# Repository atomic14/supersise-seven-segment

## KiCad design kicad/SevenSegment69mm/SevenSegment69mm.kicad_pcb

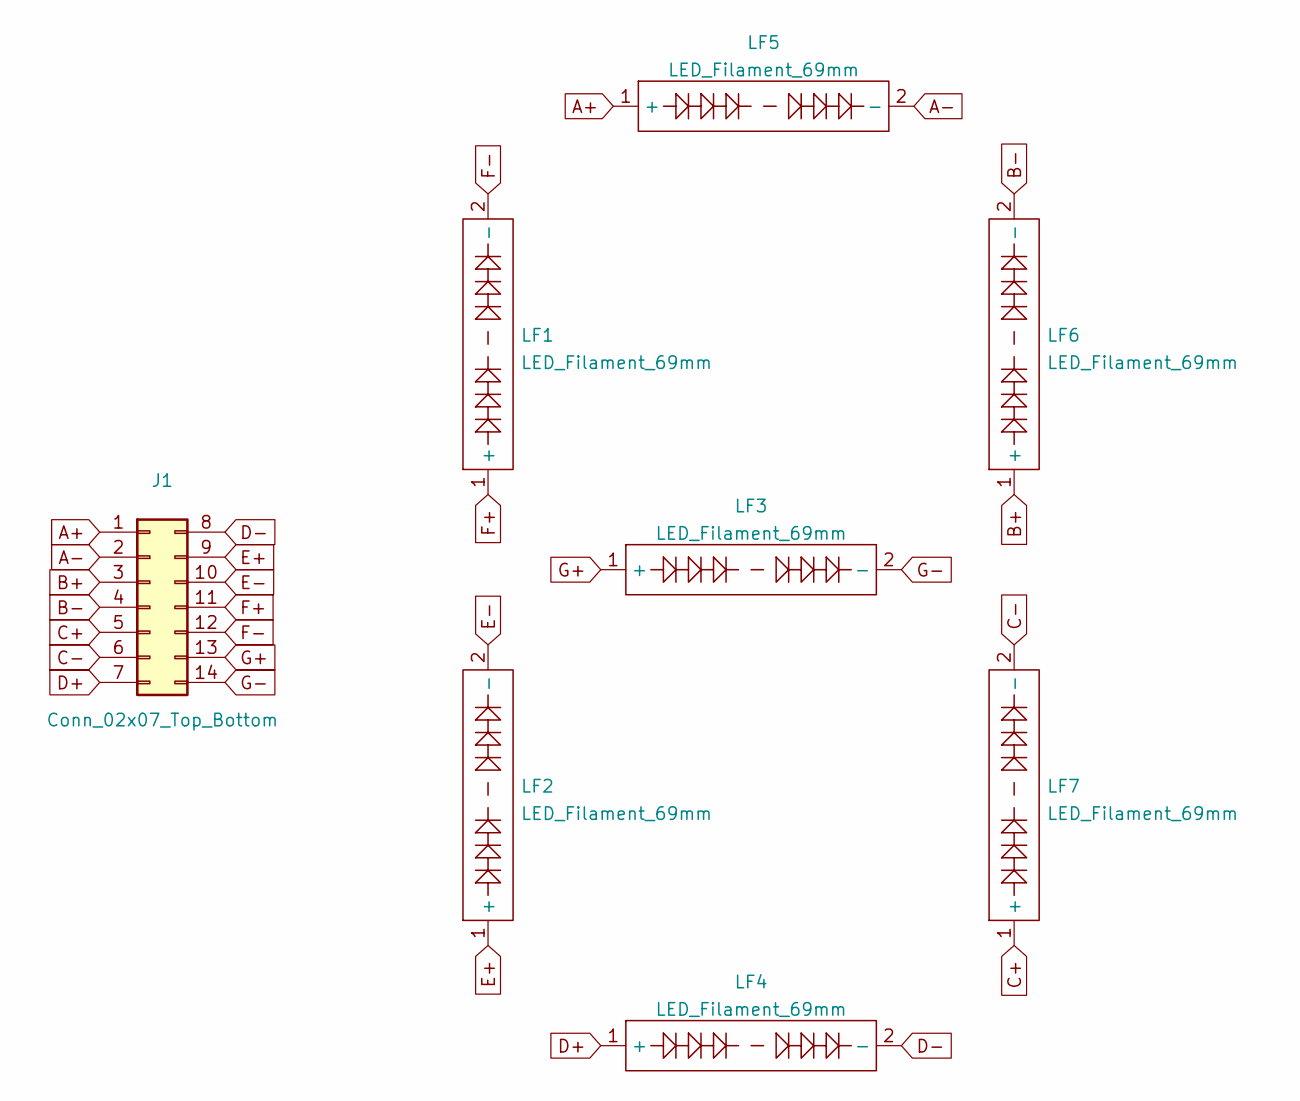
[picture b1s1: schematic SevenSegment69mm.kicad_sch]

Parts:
J1: Conn_02x07_Top_Bottom; PinHeader_2x07_P2.54mm_Horizontal
LF1, LF2, LF3, LF4, LF5, LF6, LF7: LED_Filament_69mm

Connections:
A+: J1.1, LF5.1 (+)
A-: J1.2, LF5.2 (-)
B+: J1.3, LF6.1 (+)
B-: J1.4, LF6.2 (-)
C+: J1.5, LF7.1 (+)
C-: J1.6, LF7.2 (-)
D+: J1.7, LF4.1 (+)
D-: J1.8, LF4.2 (-)
E+: J1.9, LF2.1 (+)
E-: J1.10, LF2.2 (-)
F+: J1.11, LF1.1 (+)
F-: J1.12, LF1.2 (-)
G+: J1.13, LF3.1 (+)
G-: J1.14, LF3.2 (-)

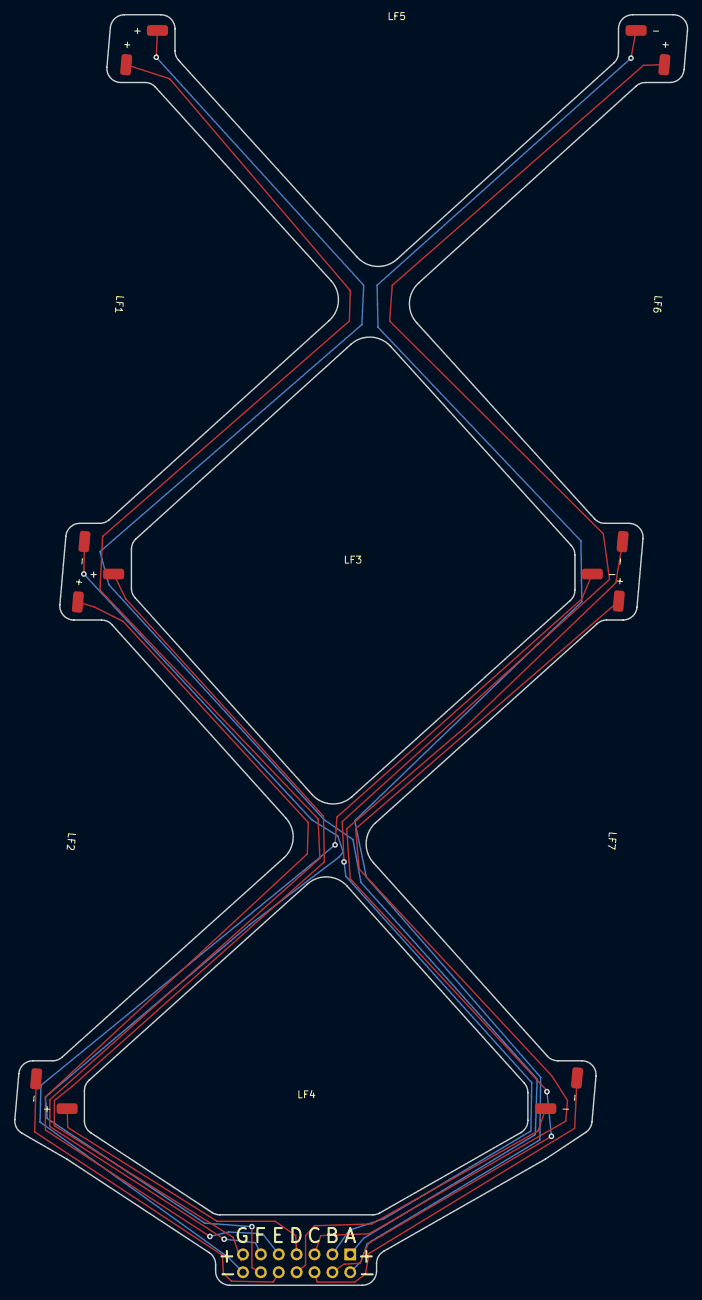
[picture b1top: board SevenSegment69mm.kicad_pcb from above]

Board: 2 copper layers, 95.6 x 180.5 mm, 8 parts (0 on the bottom side), 14 nets.

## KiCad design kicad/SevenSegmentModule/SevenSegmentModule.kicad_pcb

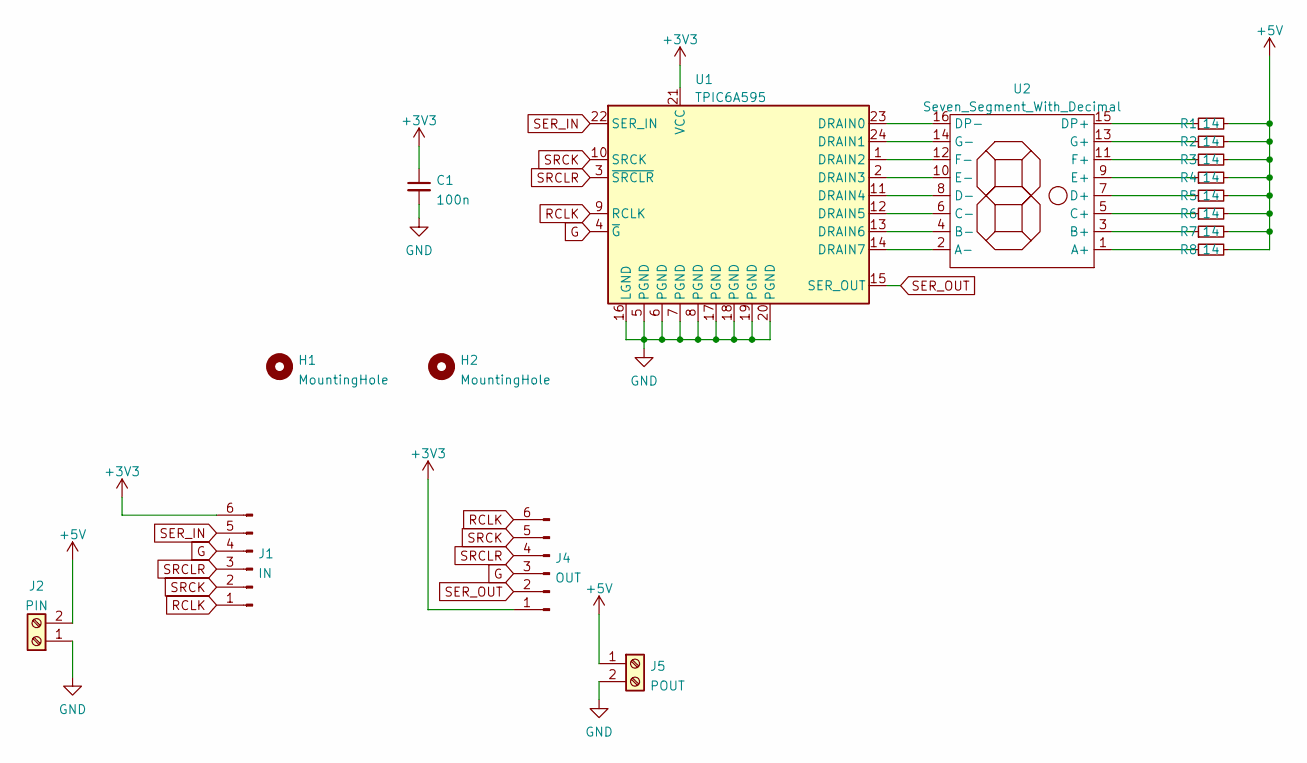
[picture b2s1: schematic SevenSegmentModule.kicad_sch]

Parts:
C1: 100n; C_0603_1608Metric
H1, H2: MountingHole; MountingHole_3.2mm_M3
J1: IN; PinHeader_1x06_P2.54mm_Horizontal
J2: PIN; TerminalBlock_Phoenix_MKDS-1,5-2-5.08_1x02_P5.08mm_Horizont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
J4: OUT; PinHeader_1x06_P2.54mm_Horizontal
J5: POUT; TerminalBlock_Phoenix_MKDS-1,5-2-5.08_1x02_P5.08mm_Horizont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
R1, R2, R3, R4, R5, R6, R7, R8: 14; R_0805_2012Metric
U1: TPIC6A595; SOIC-24W_7.5x15.4mm_P1.27mm
U2: Seven_Segment_With_Decimal; Segen_Segment_69mm_with_dp

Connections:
+3V3: C1.1, J1.6, J4.1, U1.21 (VCC)
+5V: J2.2, J5.1, R1.2, R2.2, R3.2, R4.2, R5.2, R6.2, R7.2, R8.2
G: J1.4, J4.3, U1.4 (~G)
GND: C1.2, J2.1, J5.2, U1.5 (PGND), U1.6 (PGND), U1.7 (PGND), U1.8 (PGND), U1.16 (LGND), U1.17 (PGND), U1.18 (PGND), U1.19 (PGND), U1.20 (PGND)
unnamed: R1.1, U2.15 (DP+)
unnamed: R2.1, U2.13 (G+)
unnamed: R3.1, U2.11 (F+)
unnamed: R4.1, U2.9 (E+)
unnamed: R5.1, U2.7 (D+)
unnamed: R6.1, U2.5 (C+)
unnamed: R7.1, U2.3 (B+)
unnamed: R8.1, U2.1 (A+)
unnamed: U1.14 (DRAIN7), U2.2 (A-)
unnamed: U1.13 (DRAIN6), U2.4 (B-)
unnamed: U1.12 (DRAIN5), U2.6 (C-)
unnamed: U1.11 (DRAIN4), U2.8 (D-)
unnamed: U1.2 (DRAIN3), U2.10 (E-)
unnamed: U1.1 (DRAIN2), U2.12 (F-)
unnamed: U1.24 (DRAIN1), U2.14 (G-)
unnamed: U1.23 (DRAIN0), U2.16 (DP-)
RCLK: J1.1, J4.6, U1.9 (RCLK)
SER_IN: J1.5, U1.22 (SER_IN)
SER_OUT: J4.2, U1.15 (SER_OUT)
SRCK: J1.2, J4.5, U1.10 (SRCK)
SRCLR: J1.3, J4.4, U1.3 (~SRCLR)

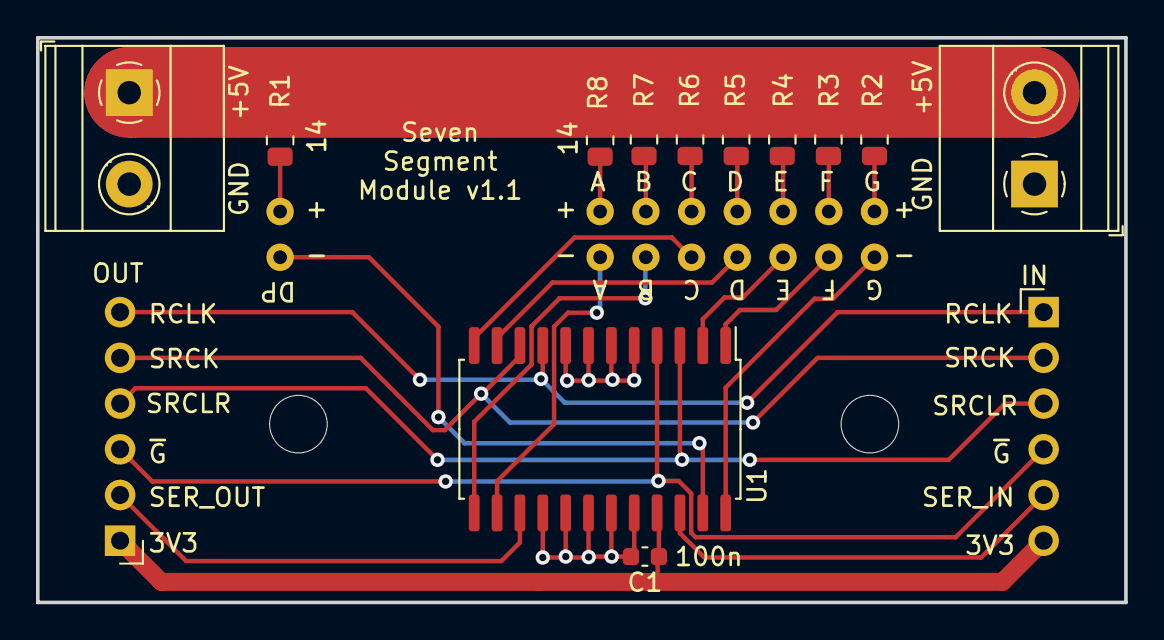
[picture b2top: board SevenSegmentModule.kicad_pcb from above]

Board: 2 copper layers, 60.5 x 31.4 mm, 17 parts (0 on the bottom side), 25 nets.

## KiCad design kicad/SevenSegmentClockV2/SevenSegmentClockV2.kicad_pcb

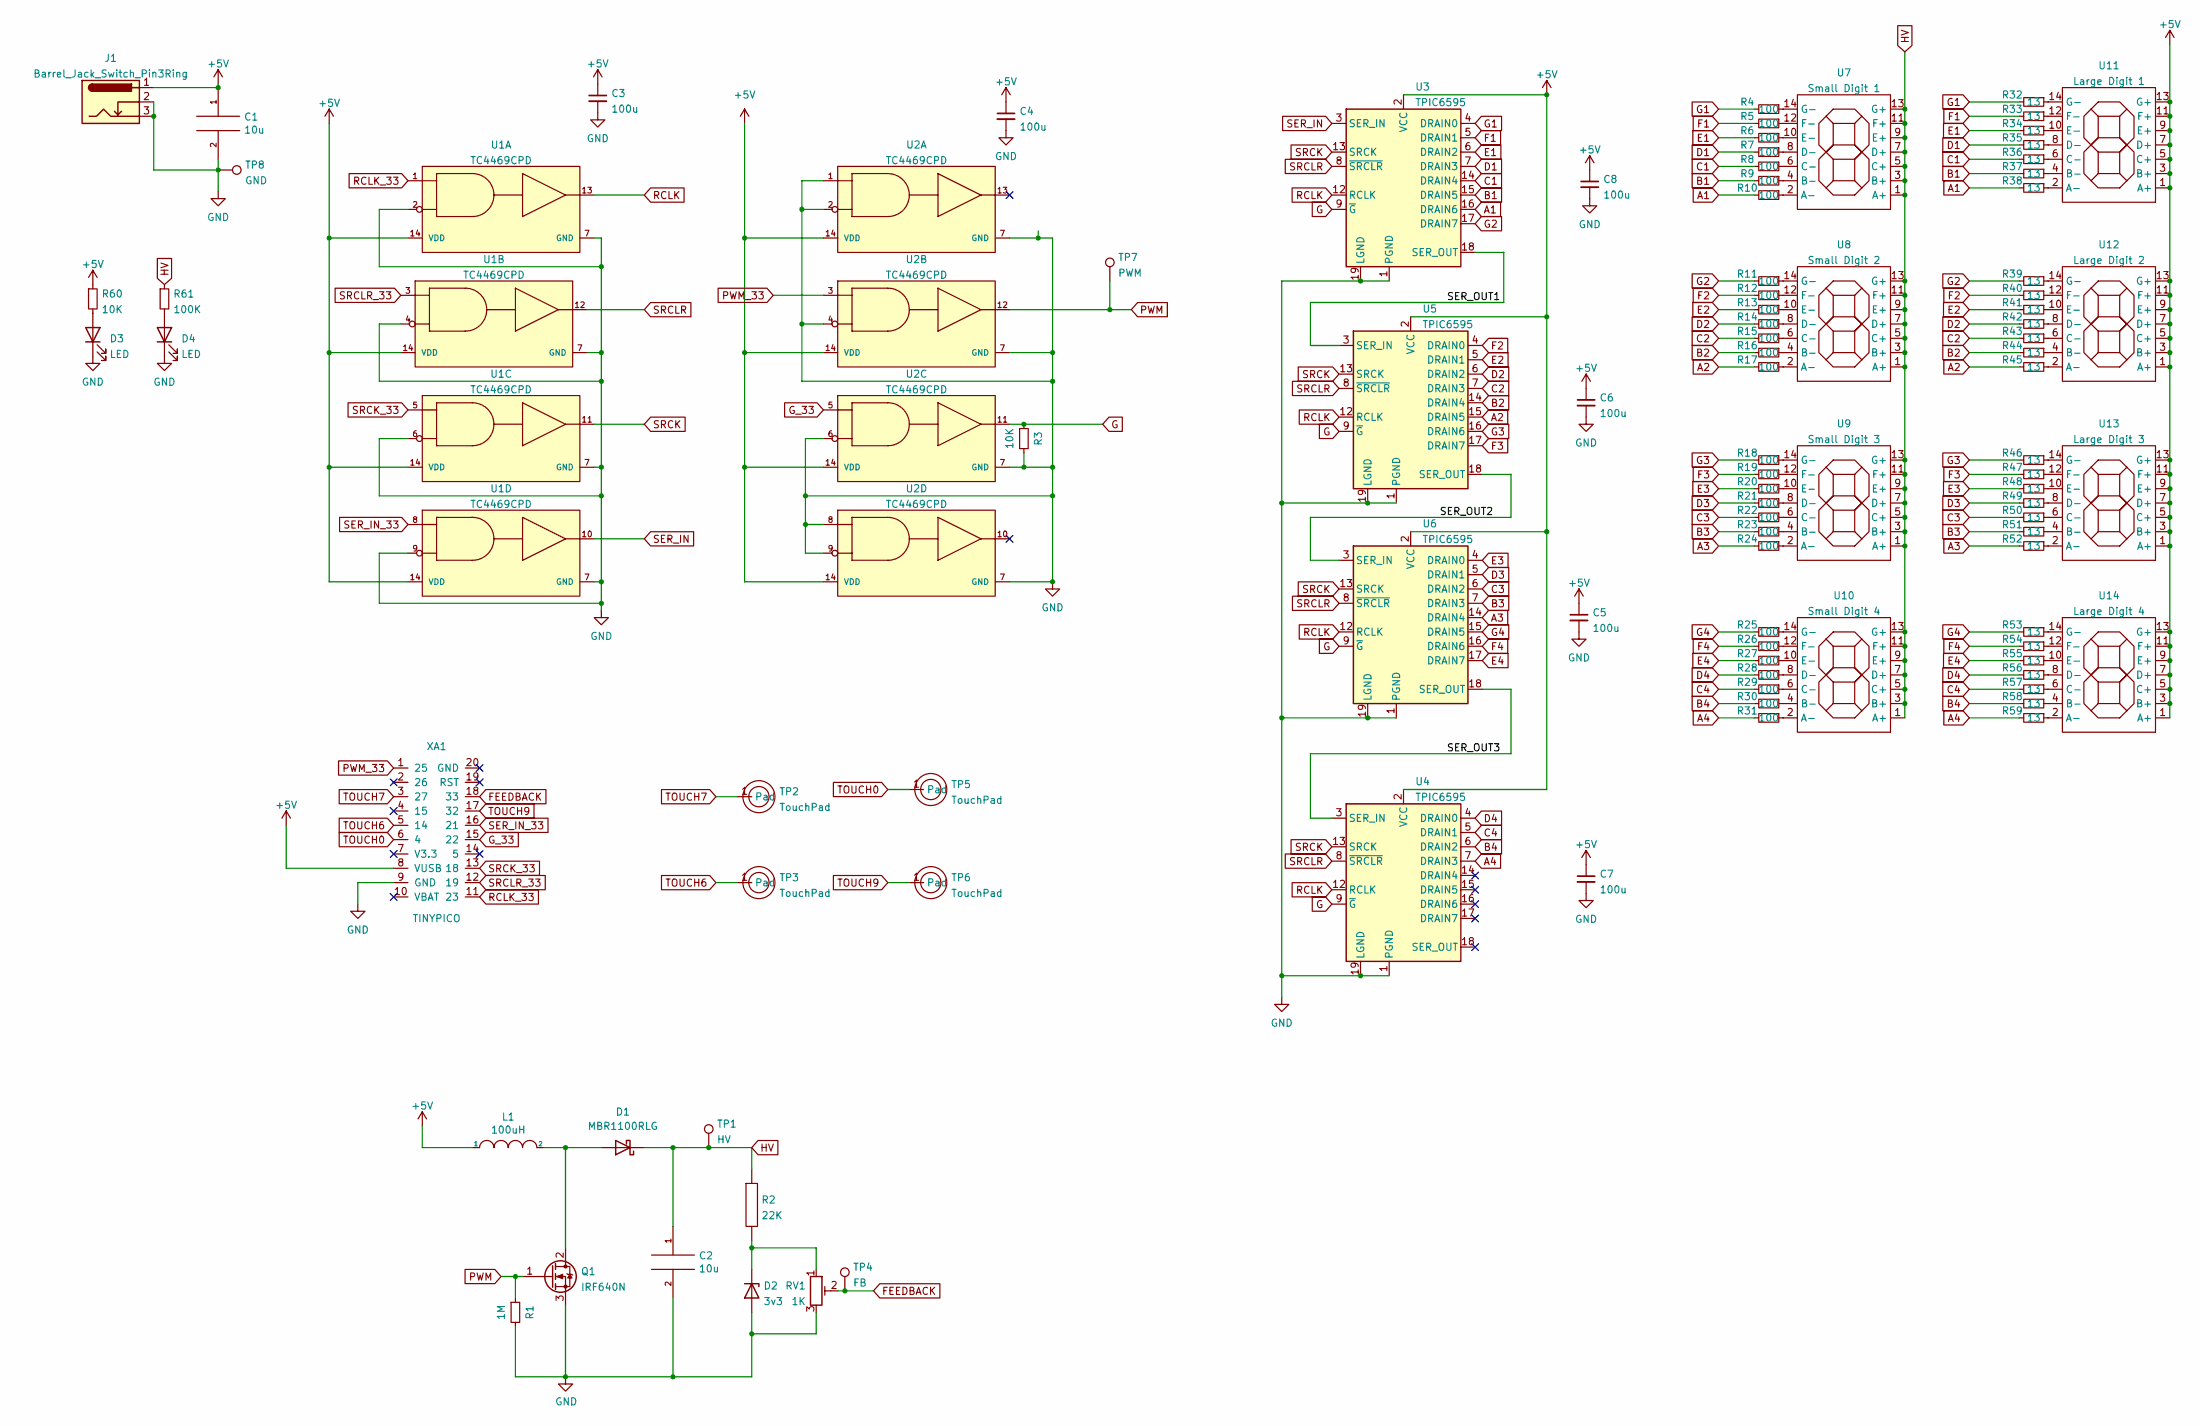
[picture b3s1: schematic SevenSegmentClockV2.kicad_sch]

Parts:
C1, C2: 10u; CP_Radial_D7.5mm_P2.50mm
C3, C4, C5, C6, C7, C8: 100u; C_0603_1608Metric_Pad1.08x0.95mm_HandSolder
D1: MBR1100RLG; D_DO-35_SOD27_P7.62mm_Horizontal
D2: 3v3; D_DO-35_SOD27_P7.62mm_Horizontal
D3, D4: LED; LED_0603_1608Metric_Pad1.05x0.95mm_HandSolder
J1: Barrel_Jack_Switch_Pin3Ring; BarrelJack_Horizontal
L1: 100uH; L_Radial_D7.5mm_P5.00mm_Fastron_07P
Q1: IRF640N; TO-220-3_Vertical
R1: 1M; R_0603_1608Metric_Pad0.98x0.95mm_HandSolder
R2: 22K; R_0603_1608Metric_Pad0.98x0.95mm_HandSolder
R3, R60: 10K; R_0603_1608Metric_Pad0.98x0.95mm_HandSolder
R4, R5, R6, R7, R8, R9, R10, R11, R12, R13, R14, R15, R16, R17, R18, R19, R20, R21, R22, R23, R24, R25, R26, R27, R28, R29, R30, R31: 100; R_Axial_DIN0207_L6.3mm_D2.5mm_P5.08mm_Vertical
R32, R33, R34, R35, R36, R37, R38, R39, R40, R41, R42, R43, R44, R45, R46, R47, R48, R49, R50, R51, R52, R53, R54, R55, R56, R57, R58, R59: 13; R_Axial_DIN0207_L6.3mm_D2.5mm_P5.08mm_Vertical
R61: 100K; R_0603_1608Metric_Pad0.98x0.95mm_HandSolder
RV1: 1K; Potentiometer_Bourns_3296W_Vertical
TP1: HV; TestPoint_Pad_4.0x4.0mm
TP2, TP3, TP5, TP6: TouchPad; TouchPad1
TP4: FB; TestPoint_Pad_4.0x4.0mm
TP7: PWM; TestPoint_Pad_4.0x4.0mm
TP8: GND; PinHeader_1x01_P2.54mm_Vertical
U1, U2: TC4469CPD; DIP-14_W7.62mm
U3, U4, U5, U6: TPIC6595; DIP-20_W7.62mm
U7: Small Digit 1; Segen_Segment_41mm
U8: Small Digit 2; Segen_Segment_41mm
U9: Small Digit 3; Segen_Segment_41mm
U10: Small Digit 4; Segen_Segment_41mm
U11: Large Digit 1; Segen_Segment_69mm
U12: Large Digit 2; Segen_Segment_69mm
U13: Large Digit 3; Segen_Segment_69mm
U14: Large Digit 4; Segen_Segment_69mm
XA1: TINYPICO

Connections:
+5V: C1.1, C3.1, C4.1, C5.1, C6.1, C7.1, C8.1, J1.1, L1.1, R60.1, U1.14 (VDD), U2.14 (VDD), U3.2 (VCC), U4.2 (VCC), U5.2 (VCC), U6.2 (VCC), U11.1 (A+), U11.3 (B+), U11.5 (C+), U11.7 (D+), U11.9 (E+), U11.11 (F+), U11.13 (G+), U12.1 (A+), U12.3 (B+), U12.5 (C+), U12.7 (D+), U12.9 (E+), U12.11 (F+), U12.13 (G+), U13.1 (A+), U13.3 (B+), U13.5 (C+), U13.7 (D+), U13.9 (E+), U13.11 (F+), U13.13 (G+), U14.1 (A+), U14.3 (B+), U14.5 (C+), U14.7 (D+), U14.9 (E+), U14.11 (F+), U14.13 (G+), XA1.8 (VUSB)
/SER_OUT1: U3.18 (SER_OUT), U5.3 (SER_IN)
/SER_OUT2: U5.18 (SER_OUT), U6.3 (SER_IN)
/SER_OUT3: U4.3 (SER_IN), U6.18 (SER_OUT)
A1: R10.2, R38.2, U3.16 (DRAIN6)
A2: R17.2, R45.2, U5.15 (DRAIN5)
A3: R24.2, R52.2, U6.14 (DRAIN4)
A4: R31.2, R59.2, U4.7 (DRAIN3)
B1: R9.2, R37.2, U3.15 (DRAIN5)
B2: R16.2, R44.2, U5.14 (DRAIN4)
B3: R23.2, R51.2, U6.7 (DRAIN3)
B4: R30.2, R58.2, U4.6 (DRAIN2)
C1: R8.2, R36.2, U3.14 (DRAIN4)
C2: R15.2, R43.2, U5.7 (DRAIN3)
C3: R22.2, R50.2, U6.6 (DRAIN2)
C4: R29.2, R57.2, U4.5 (DRAIN1)
D1: R7.2, R35.2, U3.7 (DRAIN3)
D2: R14.2, R42.2, U5.6 (DRAIN2)
D3: R21.2, R49.2, U6.5 (DRAIN1)
D4: R28.2, R56.2, U4.4 (DRAIN0)
E1: R6.2, R34.2, U3.6 (DRAIN2)
E2: R13.2, R41.2, U5.5 (DRAIN1)
E3: R20.2, R48.2, U6.4 (DRAIN0)
E4: R27.2, R55.2, U6.17 (DRAIN7)
F1: R5.2, R33.2, U3.5 (DRAIN1)
F2: R12.2, R40.2, U5.4 (DRAIN0)
F3: R19.2, R47.2, U5.17 (DRAIN7)
F4: R26.2, R54.2, U6.16 (DRAIN6)
FEEDBACK: RV1.2, TP4.1, XA1.18 (33)
G: R3.1, U2.11 (3Y), U3.9 (~G), U4.9 (~G), U5.9 (~G), U6.9 (~G)
G1: R4.2, R32.2, U3.4 (DRAIN0)
G2: R11.2, R39.2, U3.17 (DRAIN7)
G3: R18.2, R46.2, U5.16 (DRAIN6)
G4: R25.2, R53.2, U6.15 (DRAIN5)
GND: C1.2, C2.2, C3.2, C4.2, C5.2, C6.2, C7.2, C8.2, D2.2 (A), D3.1 (K), D4.1 (K), J1.2, J1.3, Q1.3 (S), R1.2, R3.2, RV1.3, TP8.1, U1.2 (1B), U1.4 (2B), U1.6 (3B), U1.7 (GND), U1.9 (4B), U2.1 (1A), U2.2 (1B), U2.4 (2B), U2.6 (3B), U2.7 (GND), U2.8 (4A), U2.9 (4B), U3.1 (PGND), U3.10 (PGND), U3.11 (PGND), U3.19 (LGND), U3.20 (PGND), U4.1 (PGND), U4.10 (PGND), U4.11 (PGND), U4.19 (LGND), U4.20 (PGND), U5.1 (PGND), U5.10 (PGND), U5.11 (PGND), U5.19 (LGND), U5.20 (PGND), U6.1 (PGND), U6.10 (PGND), U6.11 (PGND), U6.19 (LGND), U6.20 (PGND), XA1.9 (GND)
G_33: U2.5 (3A), XA1.15 (22)
HV: C2.1, D1.1 (K), R2.1, R61.1, TP1.1, U7.1 (A+), U7.3 (B+), U7.5 (C+), U7.7 (D+), U7.9 (E+), U7.11 (F+), U7.13 (G+), U8.1 (A+), U8.3 (B+), U8.5 (C+), U8.7 (D+), U8.9 (E+), U8.11 (F+), U8.13 (G+), U9.1 (A+), U9.3 (B+), U9.5 (C+), U9.7 (D+), U9.9 (E+), U9.11 (F+), U9.13 (G+), U10.1 (A+), U10.3 (B+), U10.5 (C+), U10.7 (D+), U10.9 (E+), U10.11 (F+), U10.13 (G+)
unnamed: D1.2 (A), L1.2, Q1.2 (D)
unnamed: D2.1 (K), R2.2, RV1.1
unnamed: D3.2 (A), R60.2
unnamed: D4.2 (A), R61.2
unnamed: R4.1, U7.14 (G-)
unnamed: R5.1, U7.12 (F-)
unnamed: R6.1, U7.10 (E-)
unnamed: R7.1, U7.8 (D-)
unnamed: R8.1, U7.6 (C-)
unnamed: R9.1, U7.4 (B-)
unnamed: R10.1, U7.2 (A-)
unnamed: R11.1, U8.14 (G-)
unnamed: R12.1, U8.12 (F-)
unnamed: R13.1, U8.10 (E-)
unnamed: R14.1, U8.8 (D-)
unnamed: R15.1, U8.6 (C-)
unnamed: R16.1, U8.4 (B-)
unnamed: R17.1, U8.2 (A-)
unnamed: R18.1, U9.14 (G-)
unnamed: R19.1, U9.12 (F-)
unnamed: R20.1, U9.10 (E-)
unnamed: R21.1, U9.8 (D-)
unnamed: R22.1, U9.6 (C-)
unnamed: R23.1, U9.4 (B-)
unnamed: R24.1, U9.2 (A-)
unnamed: R25.1, U10.14 (G-)
unnamed: R26.1, U10.12 (F-)
unnamed: R27.1, U10.10 (E-)
unnamed: R28.1, U10.8 (D-)
unnamed: R29.1, U10.6 (C-)
unnamed: R30.1, U10.4 (B-)
unnamed: R31.1, U10.2 (A-)
unnamed: R32.1, U11.14 (G-)
unnamed: R33.1, U11.12 (F-)
unnamed: R34.1, U11.10 (E-)
unnamed: R35.1, U11.8 (D-)
unnamed: R36.1, U11.6 (C-)
unnamed: R37.1, U11.4 (B-)
unnamed: R38.1, U11.2 (A-)
unnamed: R39.1, U12.14 (G-)
unnamed: R40.1, U12.12 (F-)
unnamed: R41.1, U12.10 (E-)
unnamed: R42.1, U12.8 (D-)
unnamed: R43.1, U12.6 (C-)
unnamed: R44.1, U12.4 (B-)
unnamed: R45.1, U12.2 (A-)
unnamed: R46.1, U13.14 (G-)
unnamed: R47.1, U13.12 (F-)
unnamed: R48.1, U13.10 (E-)
unnamed: R49.1, U13.8 (D-)
unnamed: R50.1, U13.6 (C-)
unnamed: R51.1, U13.4 (B-)
unnamed: R52.1, U13.2 (A-)
unnamed: R53.1, U14.14 (G-)
unnamed: R54.1, U14.12 (F-)
unnamed: R55.1, U14.10 (E-)
unnamed: R56.1, U14.8 (D-)
unnamed: R57.1, U14.6 (C-)
unnamed: R58.1, U14.4 (B-)
unnamed: R59.1, U14.2 (A-)
PWM: Q1.1 (G), R1.1, TP7.1, U2.12 (2Y)
PWM_33: U2.3 (2A), XA1.1 (25)
RCLK: U1.13 (1Y), U3.12 (RCLK), U4.12 (RCLK), U5.12 (RCLK), U6.12 (RCLK)
RCLK_33: U1.1 (1A), XA1.11 (23)
SER_IN: U1.10 (4Y), U3.3 (SER_IN)
SER_IN_33: U1.8 (4A), XA1.16 (21)
SRCK: U1.11 (3Y), U3.13 (SRCK), U4.13 (SRCK), U5.13 (SRCK), U6.13 (SRCK)
SRCK_33: U1.5 (3A), XA1.13 (18)
SRCLR: U1.12 (2Y), U3.8 (~SRCLR), U4.8 (~SRCLR), U5.8 (~SRCLR), U6.8 (~SRCLR)
SRCLR_33: U1.3 (2A), XA1.12 (19)
TOUCH0: TP5.1 (Pad), XA1.6 (4)
TOUCH6: TP3.1 (Pad), XA1.5 (14)
TOUCH7: TP2.1 (Pad), XA1.3 (27)
TOUCH9: TP6.1 (Pad), XA1.17 (32)

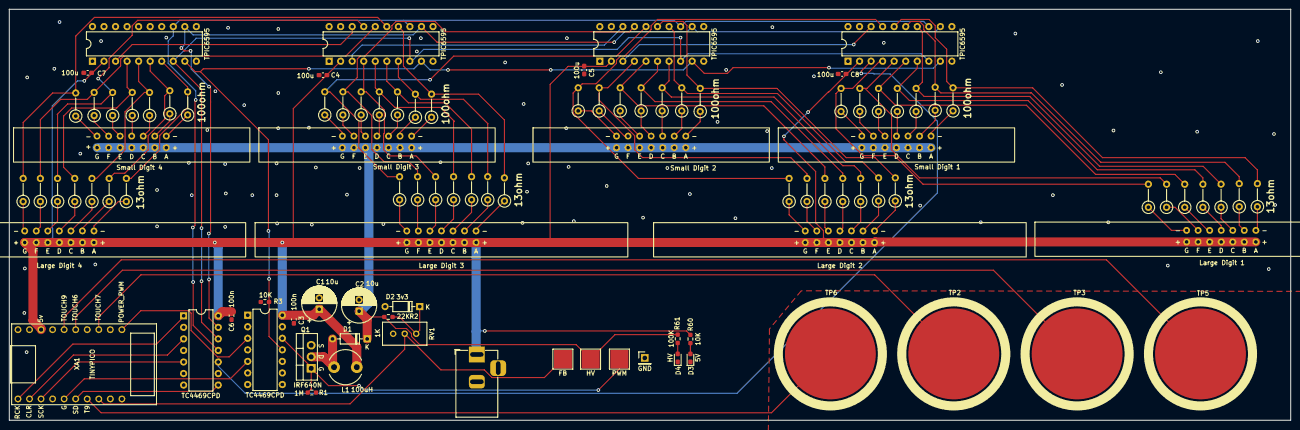
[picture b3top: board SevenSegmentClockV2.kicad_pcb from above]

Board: 2 copper layers, 281.9 x 90.4 mm, 100 parts (0 on the bottom side), 111 nets.

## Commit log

2021-12-27 Kind of working
2021-12-28 All working with integral approach
2022-01-01 Works with digits
2022-01-01 Get rid of integral
2022-01-02 bump up the frequency
2022-01-03 More tweaks
2022-03-03 Initial cut of digi driving
2022-03-07 Untested
2022-03-07 power supply working
2022-03-12 Moved to firmware folder
2022-03-12 Adds kicad files
2022-03-12 Adds README file
2022-03-12 Put readme in correct place
2022-03-12 Create LICENSE
2022-03-28 WIP - seven segment modules and decimal place
2022-06-29 Add modular PCBs and cleanup backups
2022-06-29 Adds the digit
